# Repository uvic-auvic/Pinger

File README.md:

# Pinger
A device that sends acoustic signals underwater using a piezo transducer.  
The piezo is driven with an H-bridge built using P-channel and N-channel mosfets.  
This revision includes:
- Pressure sensor
- Humidity sensor
- stm microcontroller

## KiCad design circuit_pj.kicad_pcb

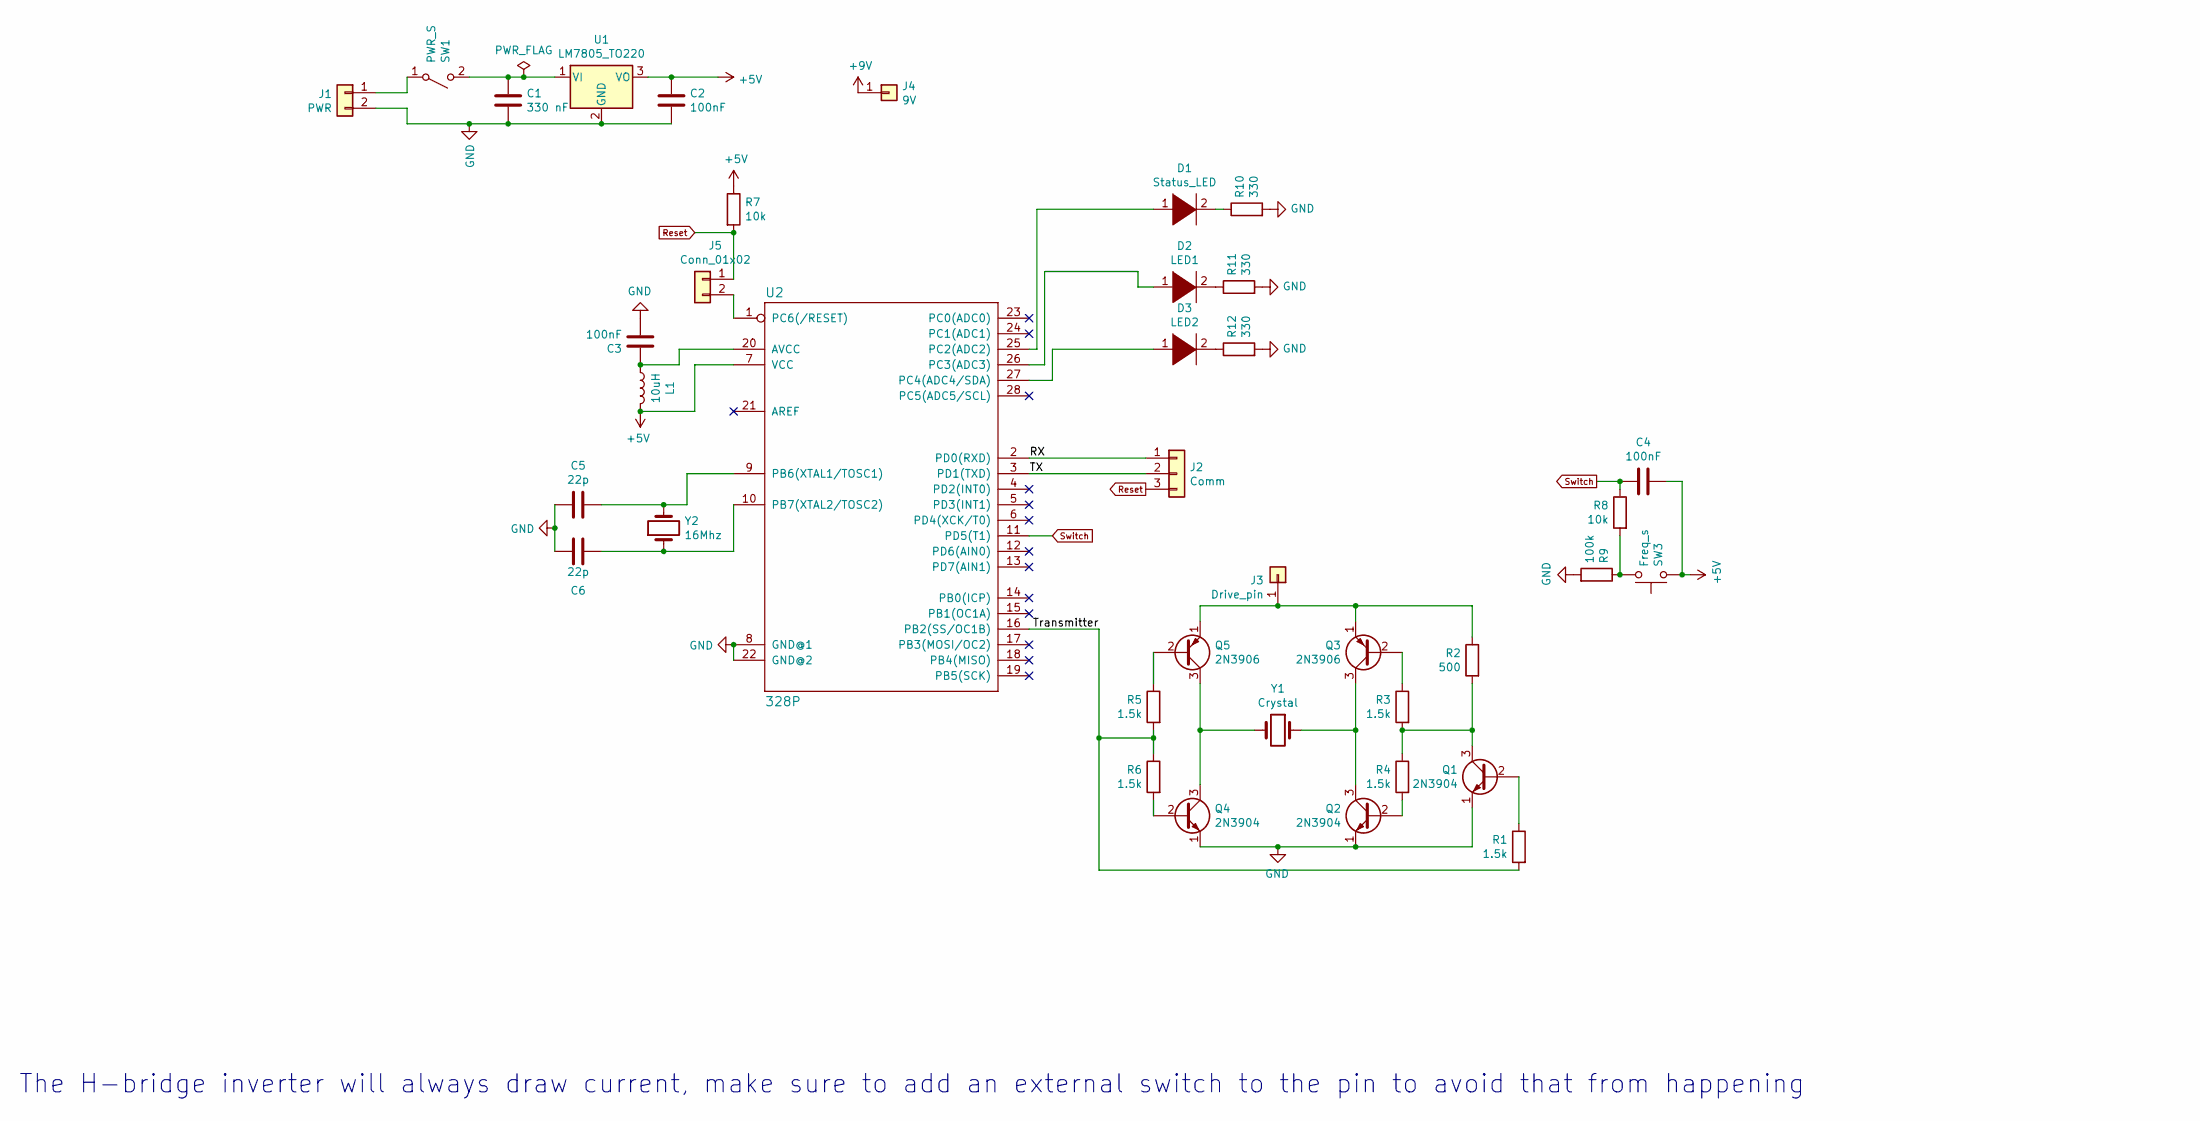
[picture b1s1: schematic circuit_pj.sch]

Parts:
C1: 330 nF; C_Axial_L5.1mm_D3.1mm_P7.50mm_Horizontal
C2, C3, C4: 100nF; C_Radial_D6.3mm_H5.0mm_P2.50mm
C5, C6: 22p; C_1210_3225Metric_Pad1.42x2.65mm_HandSolder
D1: Status_LED; LED_D5.0mm
D2: LED1; LED_D5.0mm
D3: LED2; LED_D5.0mm
J1: PWR; TerminalBlock_TE_282834-2_1x02_P2.54mm_Horizontal
J2: Comm; TerminalBlock_TE_282834-3_1x03_P2.54mm_Horizontal
J3: Drive_pin; PinHeader_1x01_P2.54mm_Vertical
J4: 9V; PinHeader_1x01_P2.54mm_Vertical
J5: Conn_01x02; PinHeader_1x02_P2.54mm_Vertical
L1: 10uH; L_TDK_SLF6028
Q1, Q2, Q4: 2N3904; TO-92_Inline
Q3, Q5: 2N3906; TO-92_Inline
R1, R3, R4, R5, R6: 1.5k; R_Axial_DIN0414_L11.9mm_D4.5mm_P15.24mm_Horizontal
R2: 500; R_Axial_DIN0414_L11.9mm_D4.5mm_P15.24mm_Horizontal
R7, R8: 10k; R_Axial_DIN0414_L11.9mm_D4.5mm_P15.24mm_Horizontal
R9: 100k; R_Axial_DIN0414_L11.9mm_D4.5mm_P15.24mm_Horizontal
R10, R11, R12: 330; R_Axial_DIN0414_L11.9mm_D4.5mm_P15.24mm_Horizontal
SW1: PWR_S; SW_DIP_SPSTx01_Slide_6.7x4.1mm_W7.62mm_P2.54mm_LowProfile
SW3: Freq_s; SW_TH_Tactile_Omron_B3F-10xx
U1: LM7805_TO220; SOT-223
U2: 328P; DIP-28_W15.24mm
Y1: Crystal; Buzzer_15x7.5RM7.6
Y2: 16Mhz; Resonator-2Pin_W10.0mm_H5.0mm

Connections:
+5V: C2.1, C4.2, L1.2, R7.1, SW3.2, U1.3 (VO), U2.7 (VCC)
+9V: J4.1
/RX: J2.1, U2.2 (PD0(RXD))
/TX: J2.2, U2.3 (PD1(TXD))
/Transmitter: R1.2, R5.2, R6.1, U2.16 (PB2(SS/OC1B))
GND: C1.1, C2.2, C3.2, C5.2, C6.1, J1.2, Q1.1 (E), Q2.1 (E), Q4.1 (E), R9.2, R10.2, R11.2, R12.2, U1.2 (GND), U2.8 (GND@1), U2.22 (GND@2)
unnamed: C1.2, SW1.2 (B), U1.1 (VI)
unnamed: C3.1, L1.1, U2.20 (AVCC)
unnamed: C5.1, U2.9 (PB6(XTAL1/TOSC1)), Y2.2
unnamed: C6.2, U2.10 (PB7(XTAL2/TOSC2)), Y2.1
unnamed: D1.1 (K), U2.25 (PC2(ADC2))
unnamed: D1.2 (A), R10.1
unnamed: D2.1 (K), U2.26 (PC3(ADC3))
unnamed: D2.2 (A), R11.1
unnamed: D3.1 (K), U2.27 (PC4(ADC4/SDA))
unnamed: D3.2 (A), R12.1
unnamed: J1.1, SW1.1 (A)
unnamed: J3.1, Q3.1 (E), Q5.1 (E), R2.1
unnamed: J5.2, U2.1 (PC6(/RESET))
unnamed: Q1.2 (B), R1.1
unnamed: Q1.3 (C), R2.2, R3.2, R4.1
unnamed: Q2.2 (B), R4.2
unnamed: Q2.3 (C), Q3.3 (C), Y1.1
unnamed: Q3.2 (B), R3.1
unnamed: Q4.2 (B), R6.2
unnamed: Q4.3 (C), Q5.3 (C), Y1.2
unnamed: Q5.2 (B), R5.1
unnamed: R8.2, R9.1, SW3.1
Reset: J2.3, J5.1, R7.2
Switch: C4.1, R8.1, U2.11 (PD5(T1))

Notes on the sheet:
The H-bridge inverter will always draw current, make sure to add an external switch to the pin to avoid that from happening

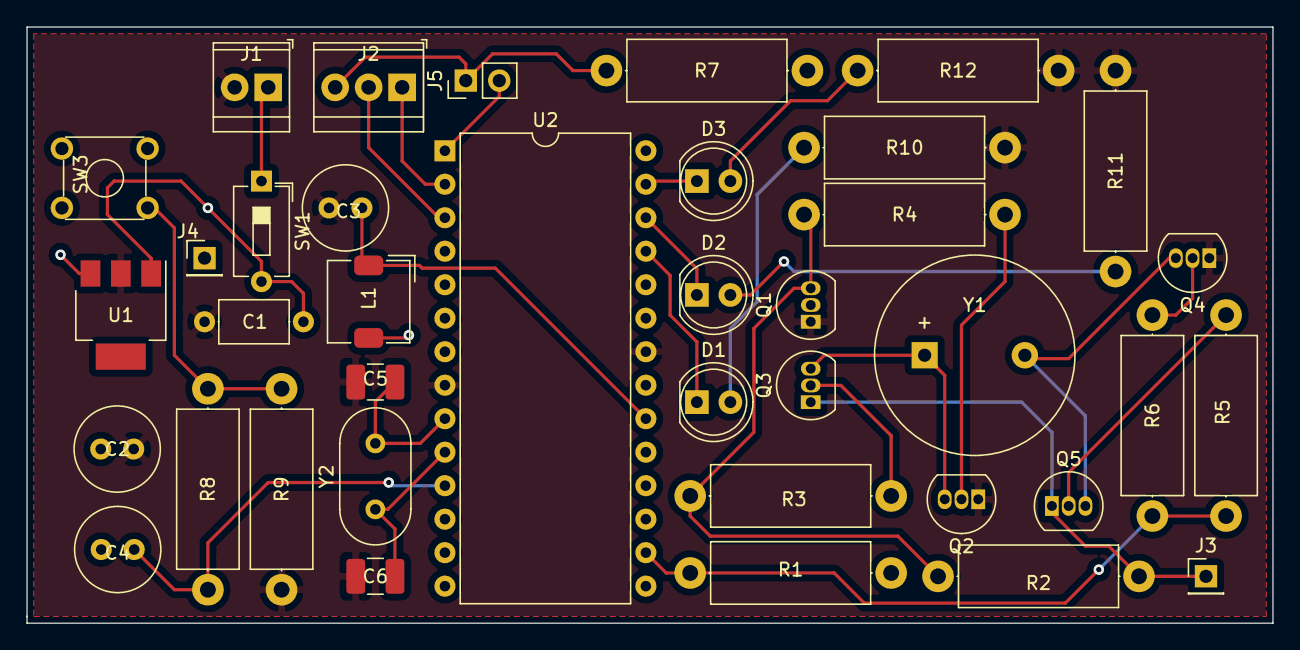
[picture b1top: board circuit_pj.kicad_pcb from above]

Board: 2 copper layers, 94.5 x 45.2 mm, 38 parts (0 on the bottom side), 29 nets.

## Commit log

2019-03-16 1st branch commit
    Fixed Charging Circuit.
    Get andy/gabe to review
    MC circuit looks good,
    DRV circuit looks good however max power is only ~2.3W with 103V bst and 25mA's. will that supply a good signal, i dont know.
2019-03-16 updates
    changed a couple of minor issues with schematic and charging circuit.
2019-03-28 Finalizing For Andy
    Heavily modified the charging circuit. Added specific symbols and footprints, including part numbers.
2019-04-22 Overhaul
    Everything has been changed. whats left to be done is changing the component designators so its easier to track them in the pcb layout tool. Need to get the dimentions of the cylinder so we can make 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
2019-06-11 Total Override
2019-06-11 amans commit
2019-06-11 Imported Pinger Files
2019-06-17 final altium pinger changes
2019-06-20 shopping list change
2020-05-15 init commit
2020-05-15 added shopping list
2020-05-17 changed reset pin from a switch to a jumper, also reorganized the schematic
2020-05-26 adjusted sch and pcb after ltspice simulation, switched PNP and NPN positions and also connected the piezo to the collector pins instead of the emitters.
2020-06-09 init commit of Rev B
2020-07-03 created new schematic
2020-07-08 changed switch
